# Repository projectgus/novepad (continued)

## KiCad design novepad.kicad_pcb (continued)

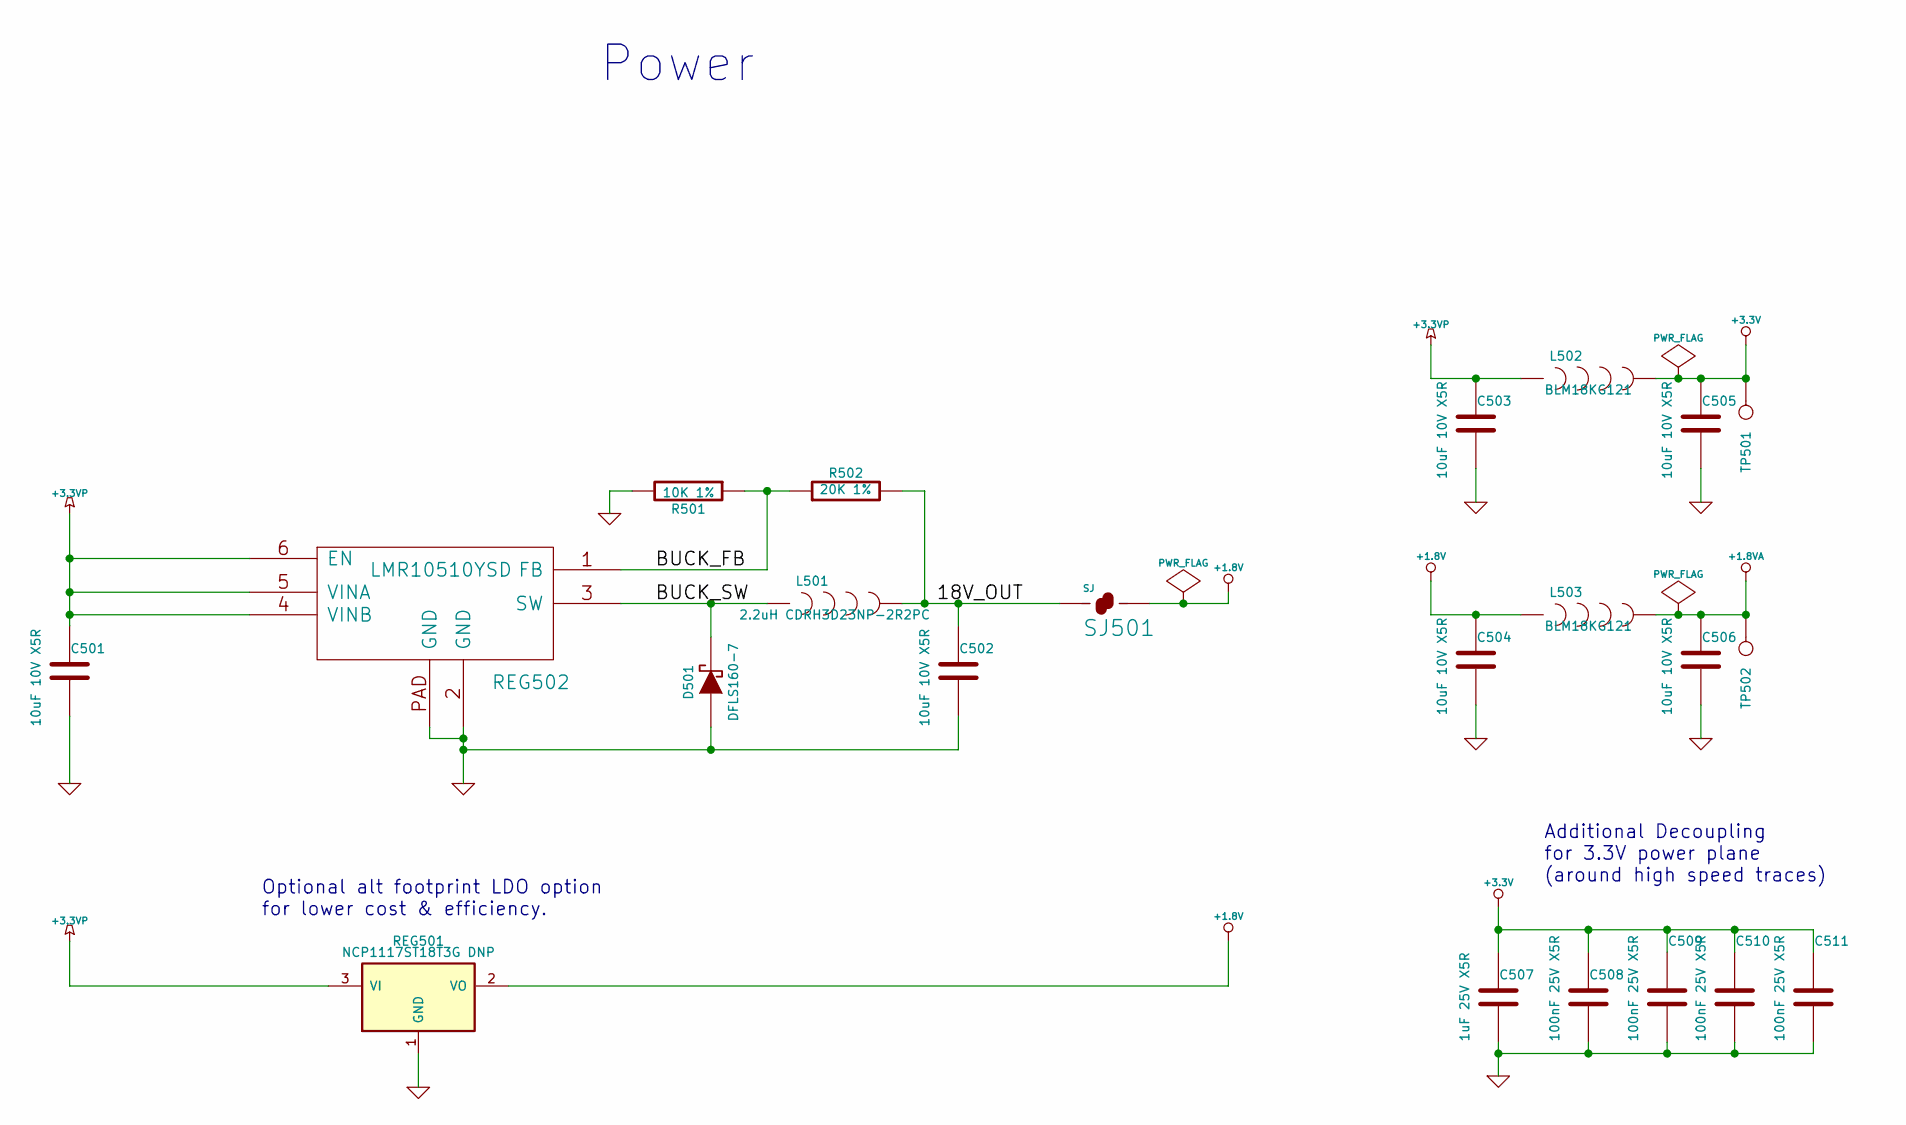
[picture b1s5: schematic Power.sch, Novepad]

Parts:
C501, C502, C503, C504, C505, C506: 10uF 10V X5R; 1206
C507: 1uF 25V X5R; SMD-0402_c
C508, C509, C510, C511: 100nF 25V X5R; SMD-0402_c
D501: DFLS160-7; POWERDI123_DIODE
L501: 2.2uH CDRH3D23NP-2R2PC; CDRH3D23_IND
L502, L503: BLM18KG121; 0603
R501: 10K 1%; 0603
R502: 20K 1%; 0603
REG501: NCP1117ST18T3G DNP; SOT223
REG502: LMR10510YSD; WSON6
SJ501: SJ; SJ_SHORTED
TP501, TP502: CONN_1; SMD_TEST_POINT

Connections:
+1.8V: C504.1, L503.1, REG501.2 (VO), SJ501.2; also elsewhere on the board
+1.8VA: C506.1, L503.2, TP502.1; also elsewhere on the board
+3.3V: C505.1, C507.1, C508.1, C509.1, C510.1, C511.1, L502.2, TP501.1; also elsewhere on the board
+3.3VP: C501.1, C503.1, L502.1, REG501.3 (VI), REG502.4 (VINB), REG502.5 (VINA), REG502.6 (EN); also elsewhere on the board
/Power/18V_OUT: C502.1, L501.2, R502.2, SJ501.1
/Power/BUCK_FB: R501.1, R502.1, REG502.1 (FB)
/Power/BUCK_SW: D501.K, L501.1, REG502.3 (SW)
GND: C501.2, C502.2, C503.2, C504.2, C505.2, C506.2, C507.2, C508.2, C509.2, C510.2, C511.2, D501.A, R501.2, REG501.1 (GND), REG502.2 (GND), REG502.PAD (GND); also elsewhere on the board

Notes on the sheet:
Optional alt footprint LDO option for lower cost & efficiency.
Power
Additional Decoupling for 3.3V power plane (around high speed traces)

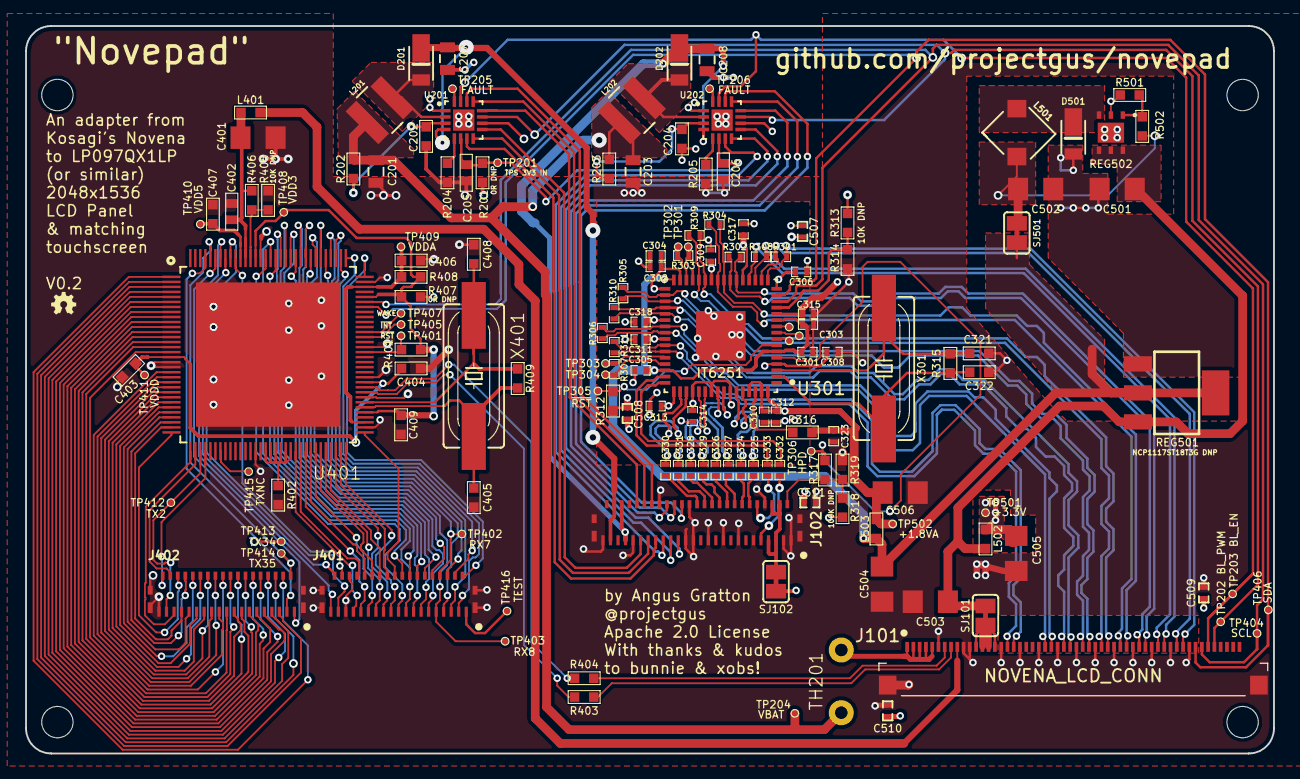
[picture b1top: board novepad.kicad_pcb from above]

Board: 4 copper layers, 99.5 x 58.0 mm, 155 parts (0 on the bottom side), 180 nets.

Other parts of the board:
LOGO_OSHW_silkscreen_2mm: val**; LOGO_OSHW_silkscreen_2mm
STENCIL8_HOLE, STENCIL8_HOLE#2, STENCIL8_HOLE#3, STENCIL8_HOLE#4: VAL**; STENCIL8_HOLE

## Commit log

2014-10-23 Initial schematic
2014-10-23 Add schematic PDF, schematic PDF generating script(!)
2014-10-23 Add a README
2014-10-23 Fix README formatting
2014-10-23 More README tweaks
2014-11-03 Swap fault/slow start FET for inrush current limiting thermistor
2014-11-03 Add initial new footprints
2014-11-03 Schematic notes
2014-11-03 Inductor choices
2014-11-03 Add shield pin to Novena LCD connector
2014-11-11 Initial footprint association, last few footprints
2014-11-11 Paper-checked connector layout
2014-11-17 First attempt at routing the high speed differential traces
2014-11-18 Super-zealous length matching version
2014-11-28 Routed, passes DRC
2014-11-28 Fix gerber defaults
2014-11-29 Update silkscreen, check solder paste layers
2014-11-29 Minor pcb cleanups
2014-11-30 More cleanup, Stencil8 mounting holes
2014-11-30 More cleanup
2014-12-01 Fix characteristic impedance, no longer require 4/4 trace/space, as per notes in README
2014-12-01 Add 4 additional 3.3V decoupling capacitors for the 3.3V power plane
2014-12-01 Bump schematic PDF
2014-12-02 Reroute tight loop for V0.2, redo length matching with tighter constraints (not for any particular reason)
